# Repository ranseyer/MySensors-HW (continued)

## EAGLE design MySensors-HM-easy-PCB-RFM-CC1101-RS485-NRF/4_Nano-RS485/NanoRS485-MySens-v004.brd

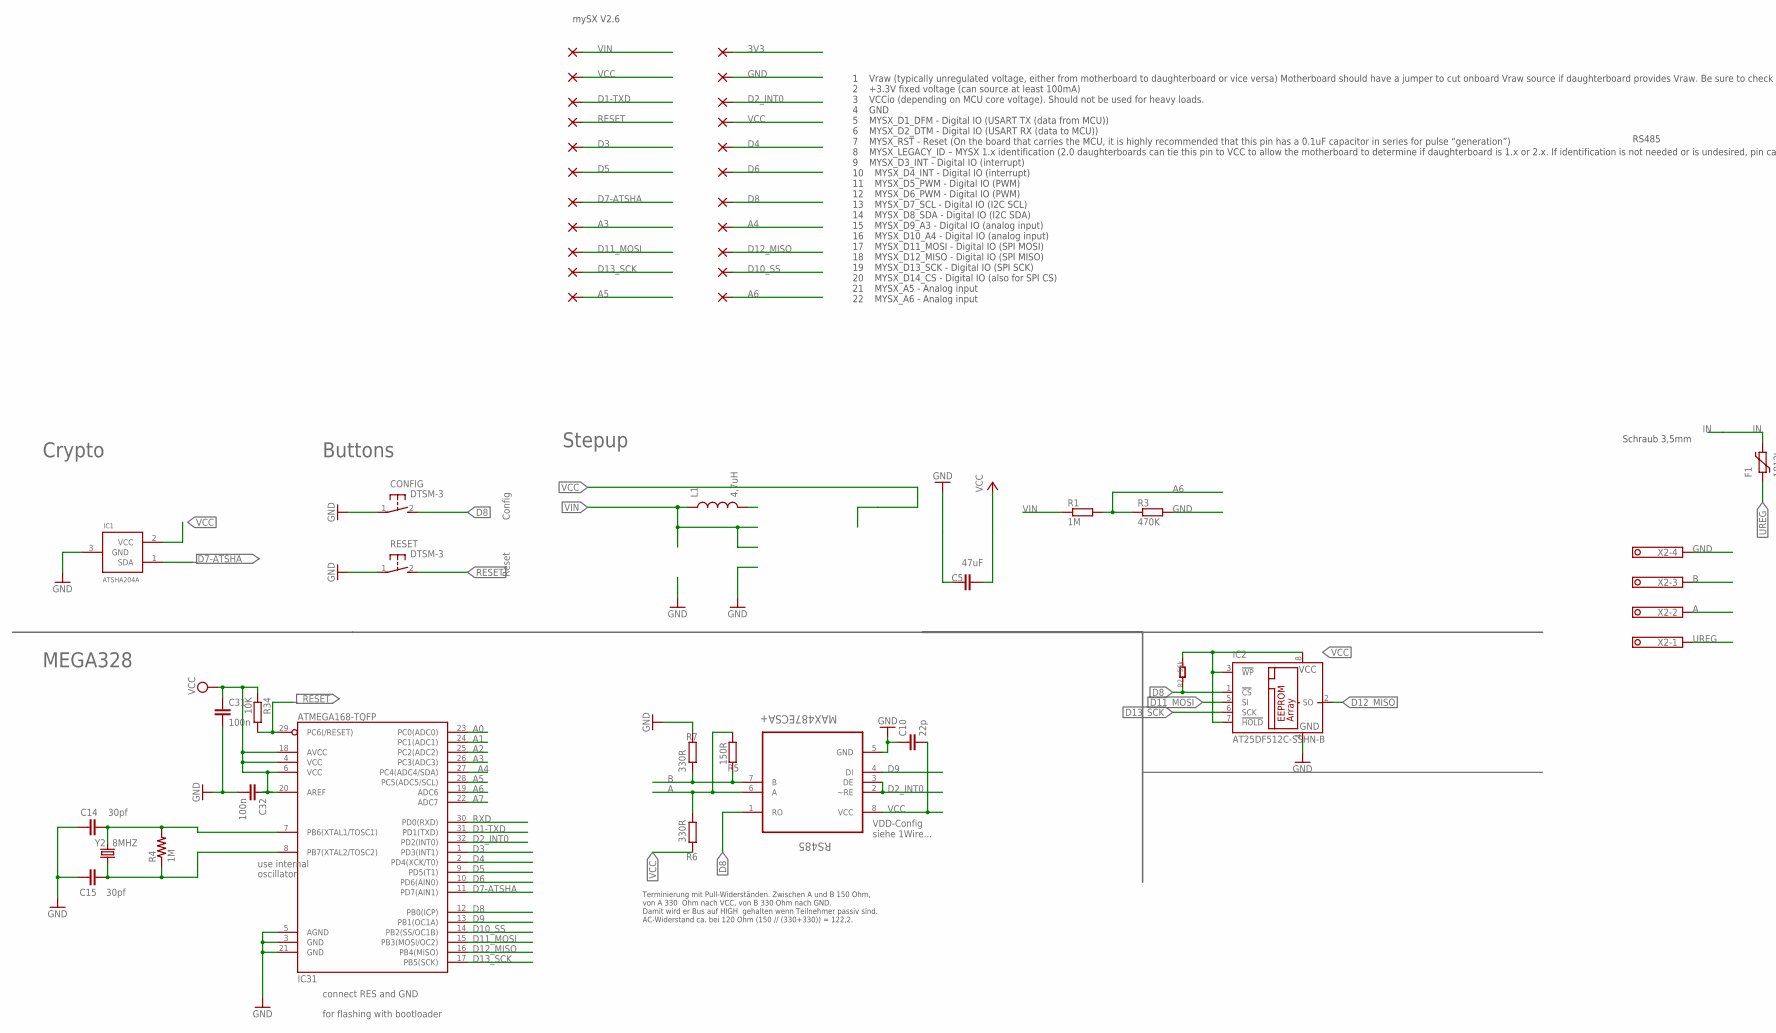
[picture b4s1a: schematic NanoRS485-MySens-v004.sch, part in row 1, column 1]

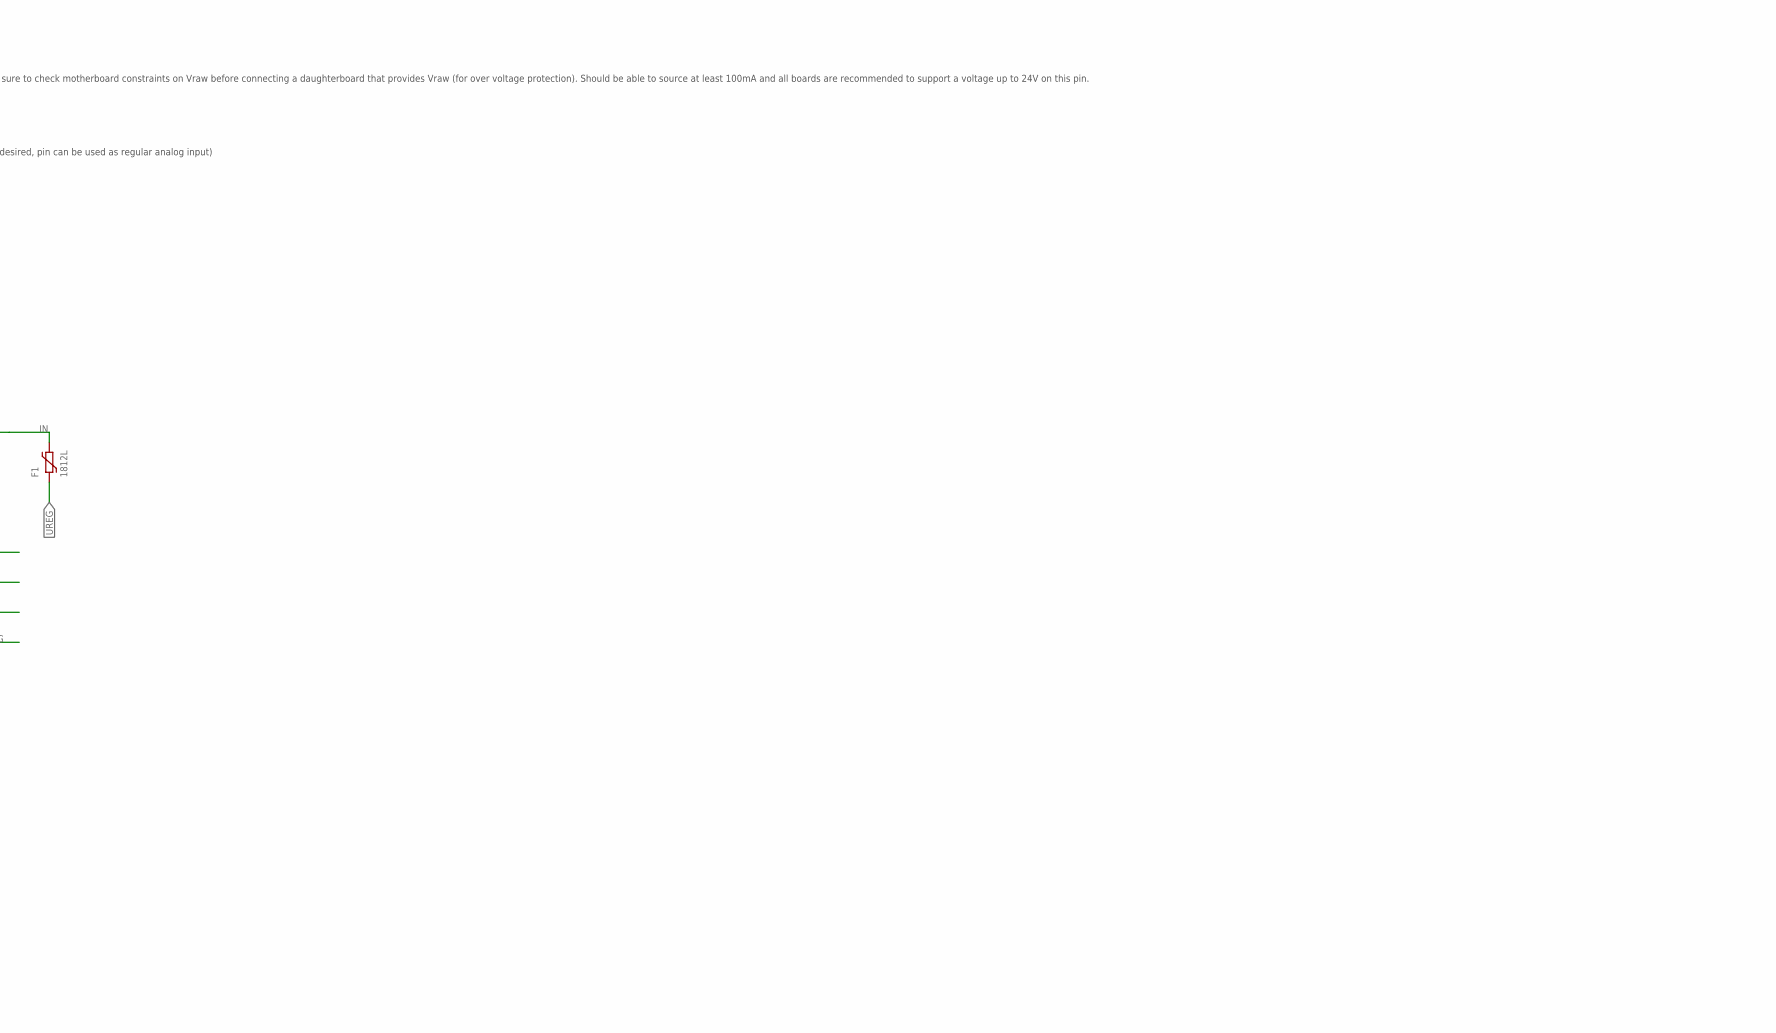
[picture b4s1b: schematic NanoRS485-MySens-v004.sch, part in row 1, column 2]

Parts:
3V3: WIREPADSMD1,27-254; SMD1,27-2,54
A3, A4, A5, A6: WIREPADSMD1,27-254; SMD1,27-2,54
C5: 47uF; C1210
C10: 22p; C0805
C14, C15: 30pf; 0805
C31, C32: 100n; C0805
CONFIG: DTSM-3
D1, D2, D3, D4, D5, D6, D7, D8, D10-SS, D11, D12, D13-SCK: WIREPADSMD1,27-254; SMD1,27-2,54
F1: 1812L
GND: WIREPADSMD1,27-254; SMD1,27-2,54
IC1: ATSHA204A; SOT23
IC2: AT25DF512C-SSHN-B; SO-08
IC31: ATMEGA168-TQFP; TQFP32-08
L1: 4,7uH; 0805
R1: 1M; R0805
R2: 56k; R0402
R3: 470K; R0805
R4: 1M; 0805
R5: 150R; R0805
R6, R7: 330R; R0805
R34: 10K; R0805
RES: WIREPADSMD1,27-254; SMD1,27-2,54
RESET: DTSM-3
RS485: MAX487ECSA+; SOIC127P600X175-8N
VCC: WIREPADSMD1,27-254; SMD1,27-2,54
VCC-LEGACY: WIREPADSMD1,27-254; SMD1,27-2,54
VIN: WIREPADSMD1,27-254; SMD1,27-2,54
X2: 1751264
Y2: 8MHZ; CRYSTAL-TXC-7A

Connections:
3V3: 3V3.1
A: R5.1, R6.2, RS485.6 (A)
A0: IC31.23 (PC0(ADC0))
A1: IC31.24 (PC1(ADC1))
A2: IC31.25 (PC2(ADC2))
A3: A3.1, IC31.26 (PC3(ADC3))
A4: A4.1, IC31.27 (PC4(ADC4/SDA))
A5: A5.1, IC31.28 (PC5(ADC5/SCL))
A6: A6.1, IC31.19 (ADC6), R1.2, R3.1
A7: IC31.22 (ADC7)
B: R5.2, R7.1, RS485.7 (B)
D1-TXD: D1.1, IC31.31 (PD1(TXD))
D2_INT0: D2.1, IC31.32 (PD2(INT0)), RS485.2 (~RE), RS485.3 (DE)
D3: D3.1, IC31.1 (PD3(INT1))
D4: D4.1, IC31.2 (PD4(XCK/T0))
D5: D5.1, IC31.9 (PD5(T1))
D6: D6.1, IC31.10 (PD6(AIN0))
D7-ATSHA: D7.1, IC1.1 (SDA), IC31.11 (PD7(AIN1))
D8: CONFIG.2, D8.1, IC2.1 (!CS), IC31.12 (PB0(ICP)), R2.1, RS485.1 (RO)
D9: IC31.13 (PB1(OC1A)), RS485.4 (DI)
D10_SS: D10-SS.1, IC31.14 (PB2(SS/OC1B))
D11_MOSI: D11.1, IC2.5 (SI), IC31.15 (PB3(MOSI/OC2))
D12_MISO: D12.1, IC2.2 (SO), IC31.16 (PB4(MISO))
D13_SCK: D13-SCK.1, IC2.6 (SCK), IC31.17 (PB5(SCK))
GND: C5.1, C10.1, C14.1, C15.1, C31.2, C32.2, CONFIG.1, GND.1, IC1.3 (GND), IC2.4 (GND), IC31.3 (GND), IC31.5 (AGND), IC31.21 (GND), R3.2, R7.2, RESET.1, RS485.5 (GND)
IN: F1.P$2 (2)
unnamed: C14.2, IC31.7 (PB6(XTAL1/TOSC1)), R4.2, Y2.P$2 (2)
unnamed: C15.2, IC31.8 (PB7(XTAL2/TOSC2)), R4.1, Y2.P$1 (1)
RESET: IC31.29 (PC6(/RESET)), R34.2, RES.1, RESET.2
RXD: IC31.30 (PD0(RXD))
UREG: F1.P$1 (1)
VCC: C5.2, C10.2, C31.1, C32.1, IC1.2 (VCC), IC2.3 (!WP), IC2.7 (!HOLD), IC2.8 (VCC), IC31.4 (VCC), IC31.6 (VCC), IC31.18 (AVCC), IC31.20 (AREF), R2.2, R6.1, R34.1, RS485.8 (VCC), VCC.1, VCC-LEGACY.1
VIN: L1.1, R1.1, VIN.1

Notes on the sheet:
MEGA328
use internal
oscillator
connect RES and GND
for flashing with bootloader
Config
Reset
Crypto
Buttons
Stepup
RS485
VDD-Config siehe 1Wire...
Terminierung mit Pull-Widerständen. Zwischen A und B 150 Ohm, von A 330 Ohm nach VCC, von B 330 Ohm nach GND. Damit wird er Bus auf HIGH gehalten wenn Teilnehmer passiv sind. AC-Widerstand ca. bei 120 Ohm (150 // (330+330)) = 122,2.
Schraub 3,5mm
1 Vraw (typically unregulated voltage, either from motherboard to daughterboard or vice versa) Motherboard should have a jumper to cut onboard Vraw source if daughterboard provides Vraw. Be sure to check motherboard constraints on Vraw before connecting a daughterboard that provides Vraw (for over 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
mySX V2.6

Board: 2 copper layers, 46 parts (21 on the bottom side), 25 nets, no tracks yet.
